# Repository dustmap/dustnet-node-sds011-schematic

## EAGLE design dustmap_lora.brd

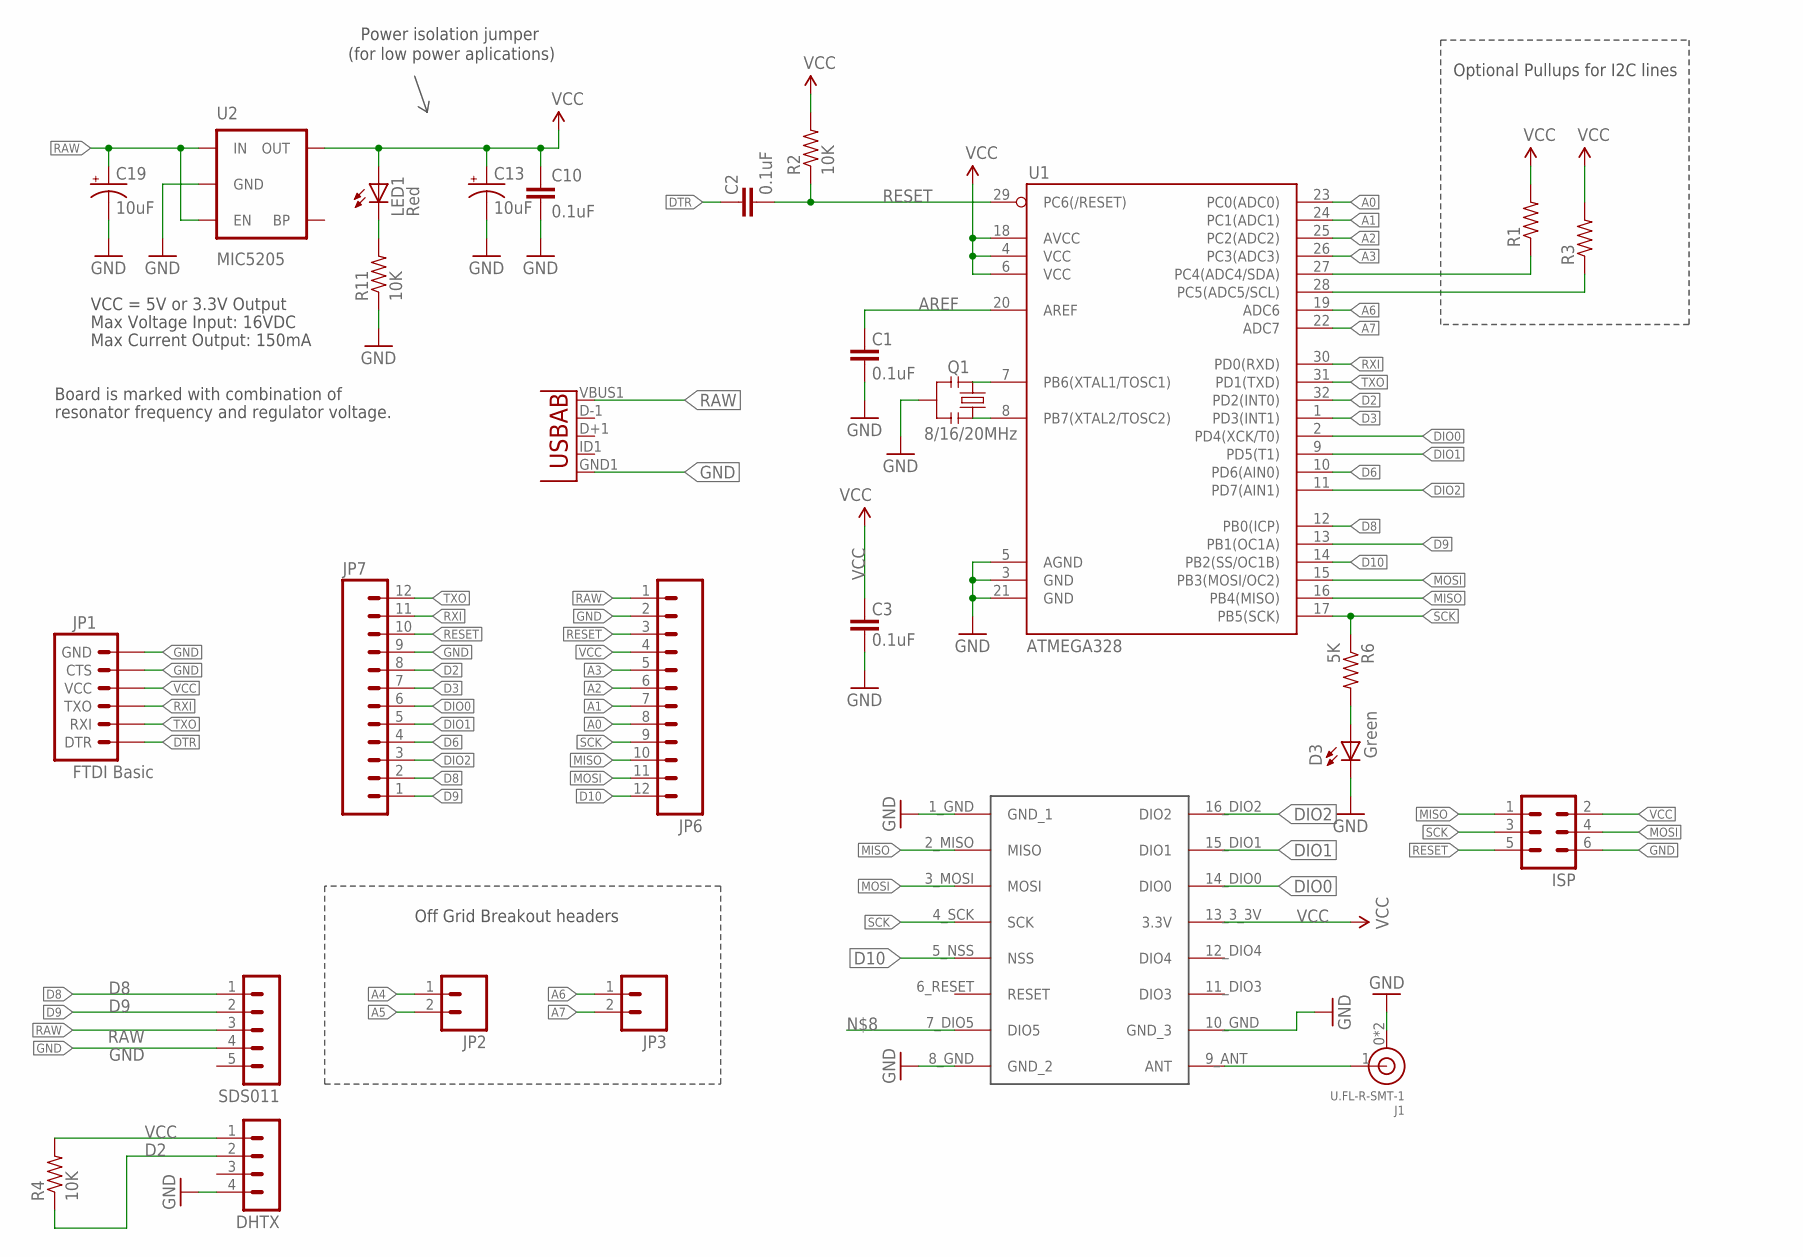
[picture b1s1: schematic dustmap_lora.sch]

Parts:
C1, C2, C3, C10: 0.1uF; 0603-CAP
C13, C19: 10uF; EIA3216
D3: Green; 0603-LED-ALT1
DHTX: MA04-1
ISP: MA03-2
J1: U.FL-R-SMT-1; U.FL
JP1: FTDI Basic; 1X06
JP2, JP3: M02PTH; 1X02
JP6, JP7: M12PTH; 1X12
LED1: Red; 0603-LED-ALT1
Q1: 8/16/20MHz; RESONATOR-SMD-1:1
R1, R3: RESISTOR0603-RES; 0603-RES
R2, R4, R11: 10K; 0603-RES
R6: 5K; 0603-RES
SDS011: MA05-1
U1: ATMEGA328; TQFP32-08
U2: MIC5205; SOT23-5
U3: USB""; USB-MICRO-SMD
U$1: RF96; SMD

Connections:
A0: JP6.8, U1.23 (PC0(ADC0))
A1: JP6.7, U1.24 (PC1(ADC1))
A2: JP6.6, U1.25 (PC2(ADC2))
A3: JP6.5, U1.26 (PC3(ADC3))
A4: JP2.1, R1.1, U1.27 (PC4(ADC4/SDA))
A5: JP2.2, R3.1, U1.28 (PC5(ADC5/SCL))
A6: JP3.1, U1.19 (ADC6)
A7: JP3.2, U1.22 (ADC7)
AREF: C1.2, U1.20 (AREF)
D2: DHTX.2, JP7.8, R4.1, U1.32 (PD2(INT0))
D3: JP7.7, U1.1 (PD3(INT1))
D6: JP7.4, U1.10 (PD6(AIN0))
D8: JP7.2, SDS011.1, U1.12 (PB0(ICP))
D9: JP7.1, SDS011.2, U1.13 (PB1(OC1A))
D10: JP6.12, U1.14 (PB2(SS/OC1B)), U$1.5_NSS (NSS)
DIO0: JP7.6, U1.2 (PD4(XCK/T0)), U$1.14_DIO0 (DIO0)
DIO1: JP7.5, U1.9 (PD5(T1)), U$1.15_DIO1 (DIO1)
DIO2: JP7.3, U1.11 (PD7(AIN1)), U$1.16_DIO2 (DIO2)
DTR: C2.2, JP1.1 (DTR)
GND: C1.1, C3.1, C10.2, C13.C (-), C19.C (-), D3.C, DHTX.4, ISP.6, J1.0 (GND), J1.2 (GND), JP1.5 (CTS), JP1.6 (GND), JP6.2, JP7.9, Q1.2, R11.1, SDS011.4, U1.3 (GND), U1.5 (AGND), U1.21 (GND), U2.2 (GND), U3.GND1 (GND), U$1.1_GND (GND_1), U$1.8_GND (GND_2), U$1.10_GND (GND_3)
MISO: ISP.1, JP6.10, U1.16 (PB4(MISO)), U$1.2_MISO (MISO)
MOSI: ISP.4, JP6.11, U1.15 (PB3(MOSI/OC2)), U$1.3_MOSI (MOSI)
unnamed: Q1.3, U1.8 (PB7(XTAL2/TOSC2))
unnamed: Q1.1, U1.7 (PB6(XTAL1/TOSC1))
unnamed: J1.1 (SIG), U$1.9_ANT (ANT)
unnamed: LED1.C, R11.2
unnamed: D3.A, R6.2
RAW: C19.A (+), JP6.1, SDS011.3, U2.1 (IN), U2.3 (EN), U3.VBUS1 (VBUS)
RESET: C2.1, ISP.5, JP6.3, JP7.10, R2.1, U1.29 (PC6(/RESET))
RXI: JP1.3 (TXO), JP7.11, U1.30 (PD0(RXD))
SCK: ISP.3, JP6.9, R6.1, U1.17 (PB5(SCK)), U$1.4_SCK (SCK)
TXO: JP1.2 (RXI), JP7.12, U1.31 (PD1(TXD))
VCC: C3.2, C10.1, C13.A (+), DHTX.1, ISP.2, JP1.4 (VCC), JP6.4, LED1.A, R1.2, R2.2, R3.2, R4.2, U1.4 (VCC), U1.6 (VCC), U1.18 (AVCC), U2.5 (OUT), U$1.13_3_3V (3.3V)

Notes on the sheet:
Max Voltage Input: 16VDC
Max Current Output: 150mA
Board is marked with combination of
resonator frequency and regulator voltage.
VCC = 5V or 3.3V Output
Optional Pullups for I2C lines
Off Grid Breakout headers
Power isolation jumper
(for low power aplications)

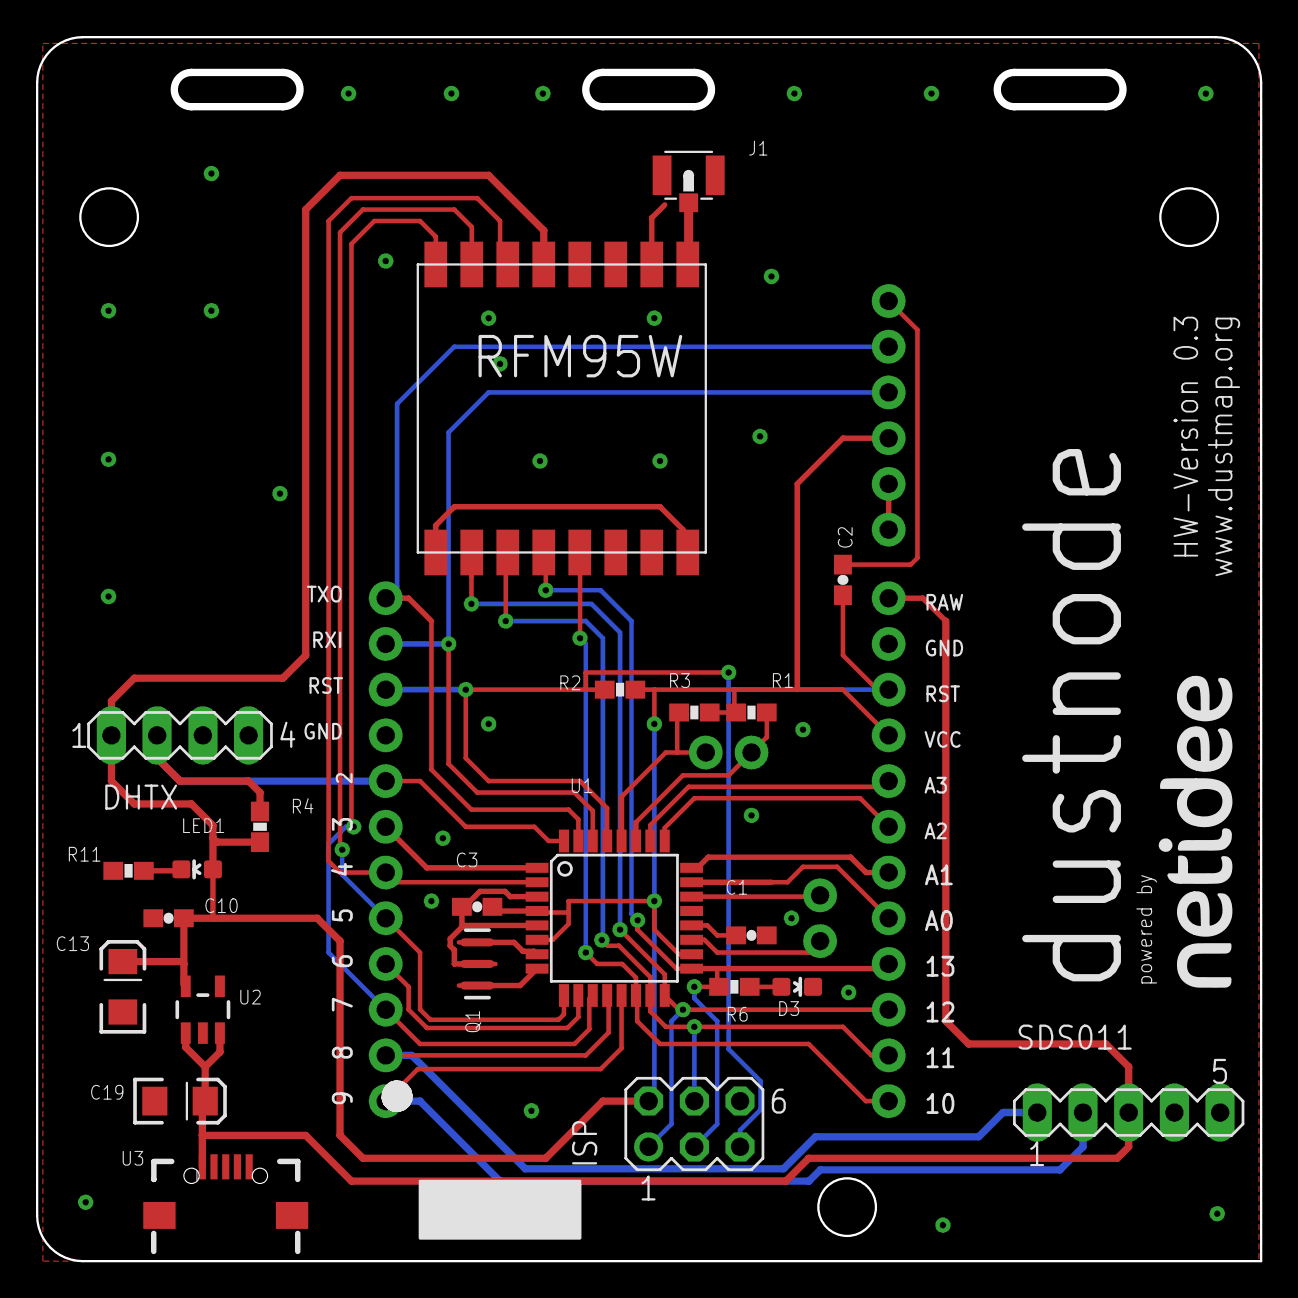
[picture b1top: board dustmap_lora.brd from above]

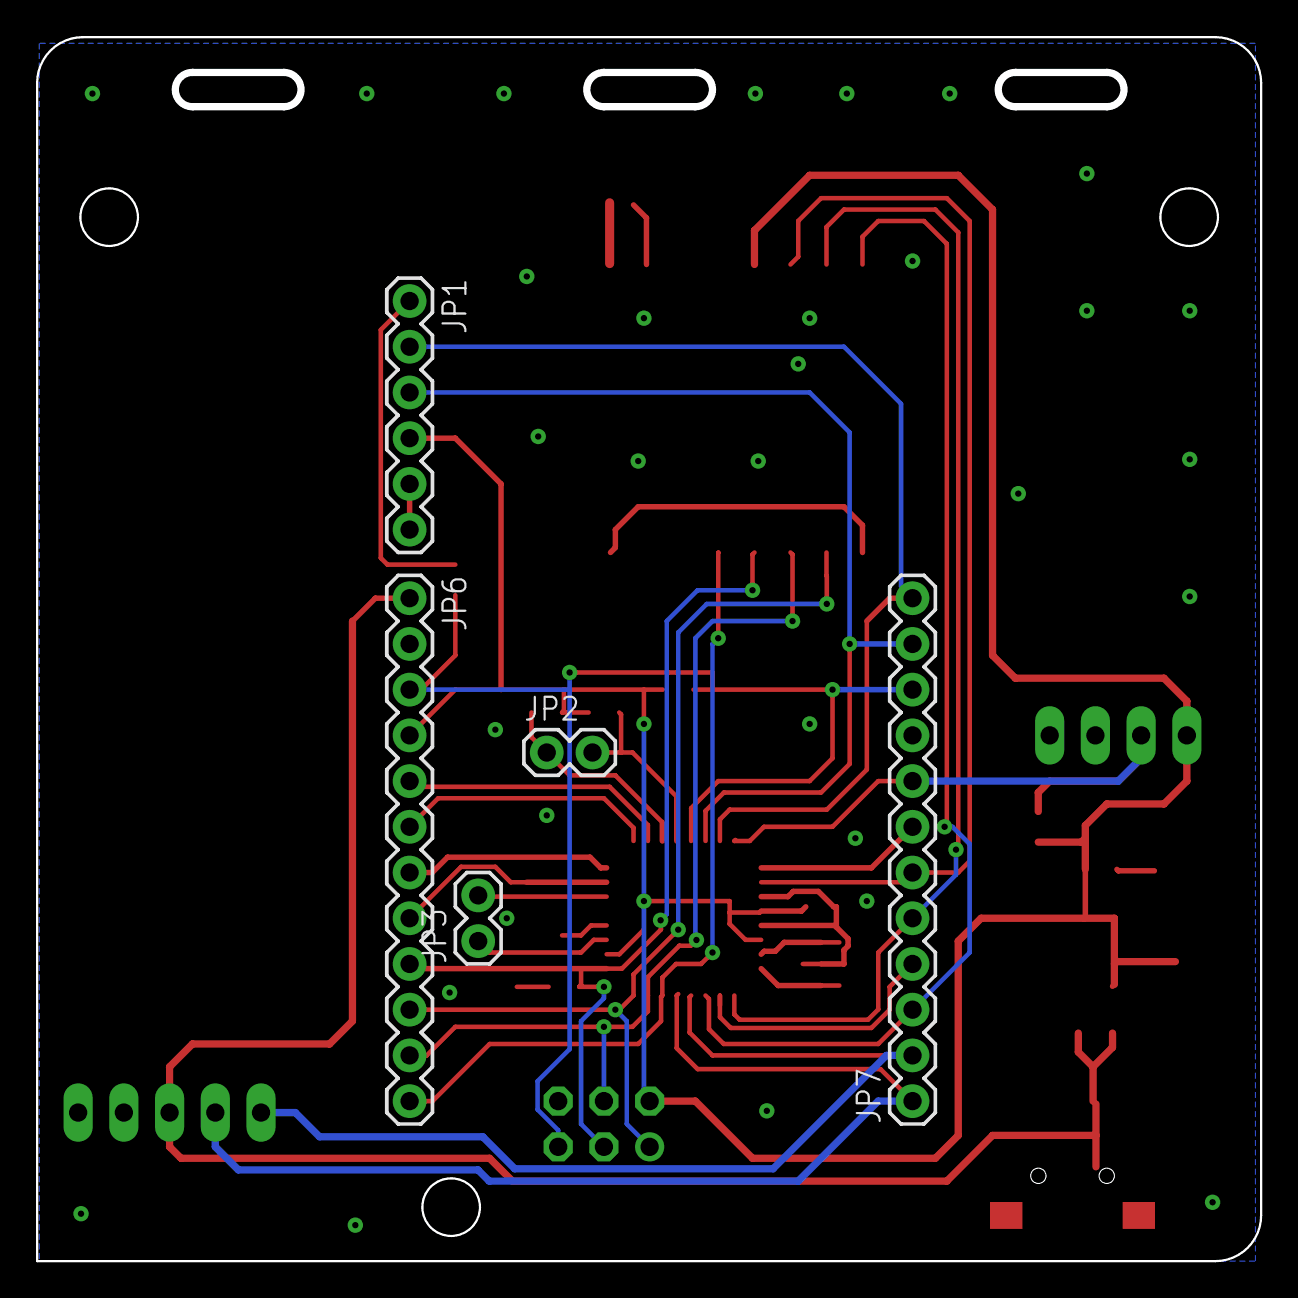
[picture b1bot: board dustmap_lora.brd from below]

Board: 2 copper layers, 67.7 x 67.7 mm, 29 parts (5 on the bottom side), 33 nets.

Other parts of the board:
U$2: SDS011

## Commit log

2019-09-02 Added CERN Open Hardware Licence
    See https://en.wikipedia.org/wiki/CERN_Open_Hardware_Licence
2019-09-02 Added Board and Schematics
2019-09-02 Added PDF
2019-09-03 Added BOM
